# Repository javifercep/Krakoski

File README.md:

# Krakoski
Kodillo compatible board

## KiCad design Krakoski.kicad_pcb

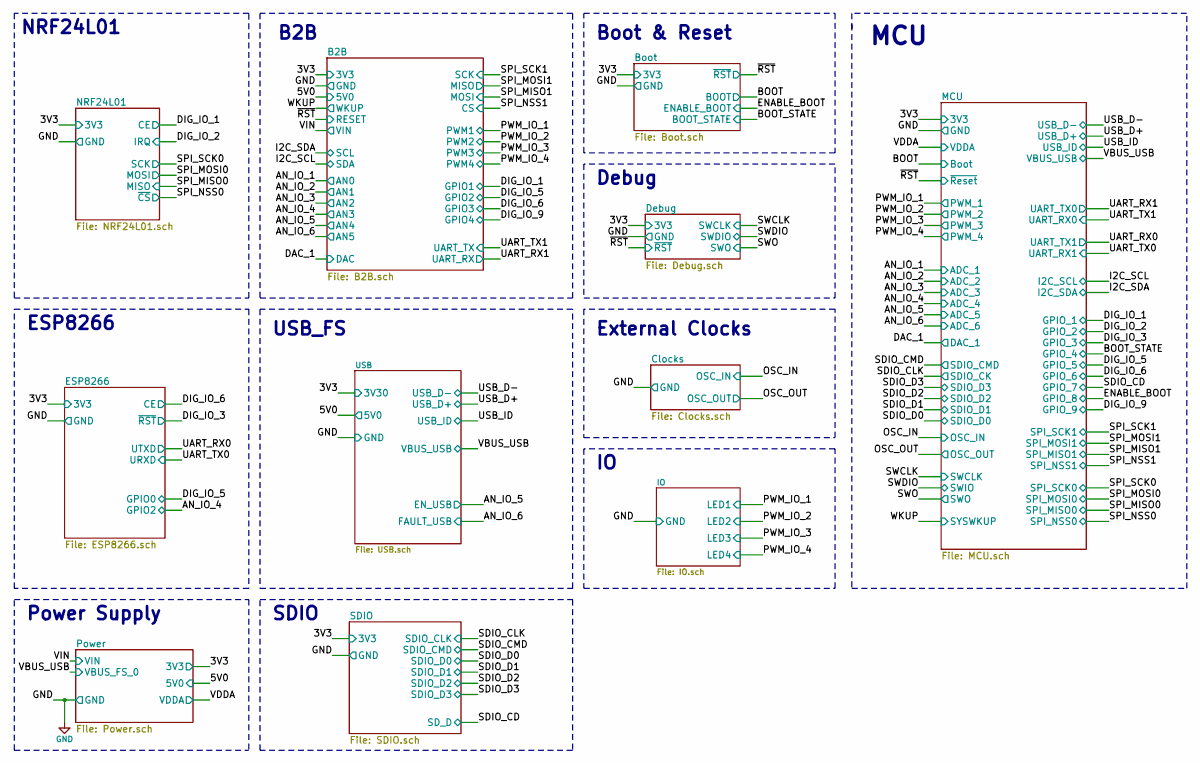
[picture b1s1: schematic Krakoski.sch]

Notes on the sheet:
Power Supply
USB_FS
Debug
External Clocks
MCU
Boot & Reset
ESP8266
B2B
NRF24L01
SDIO

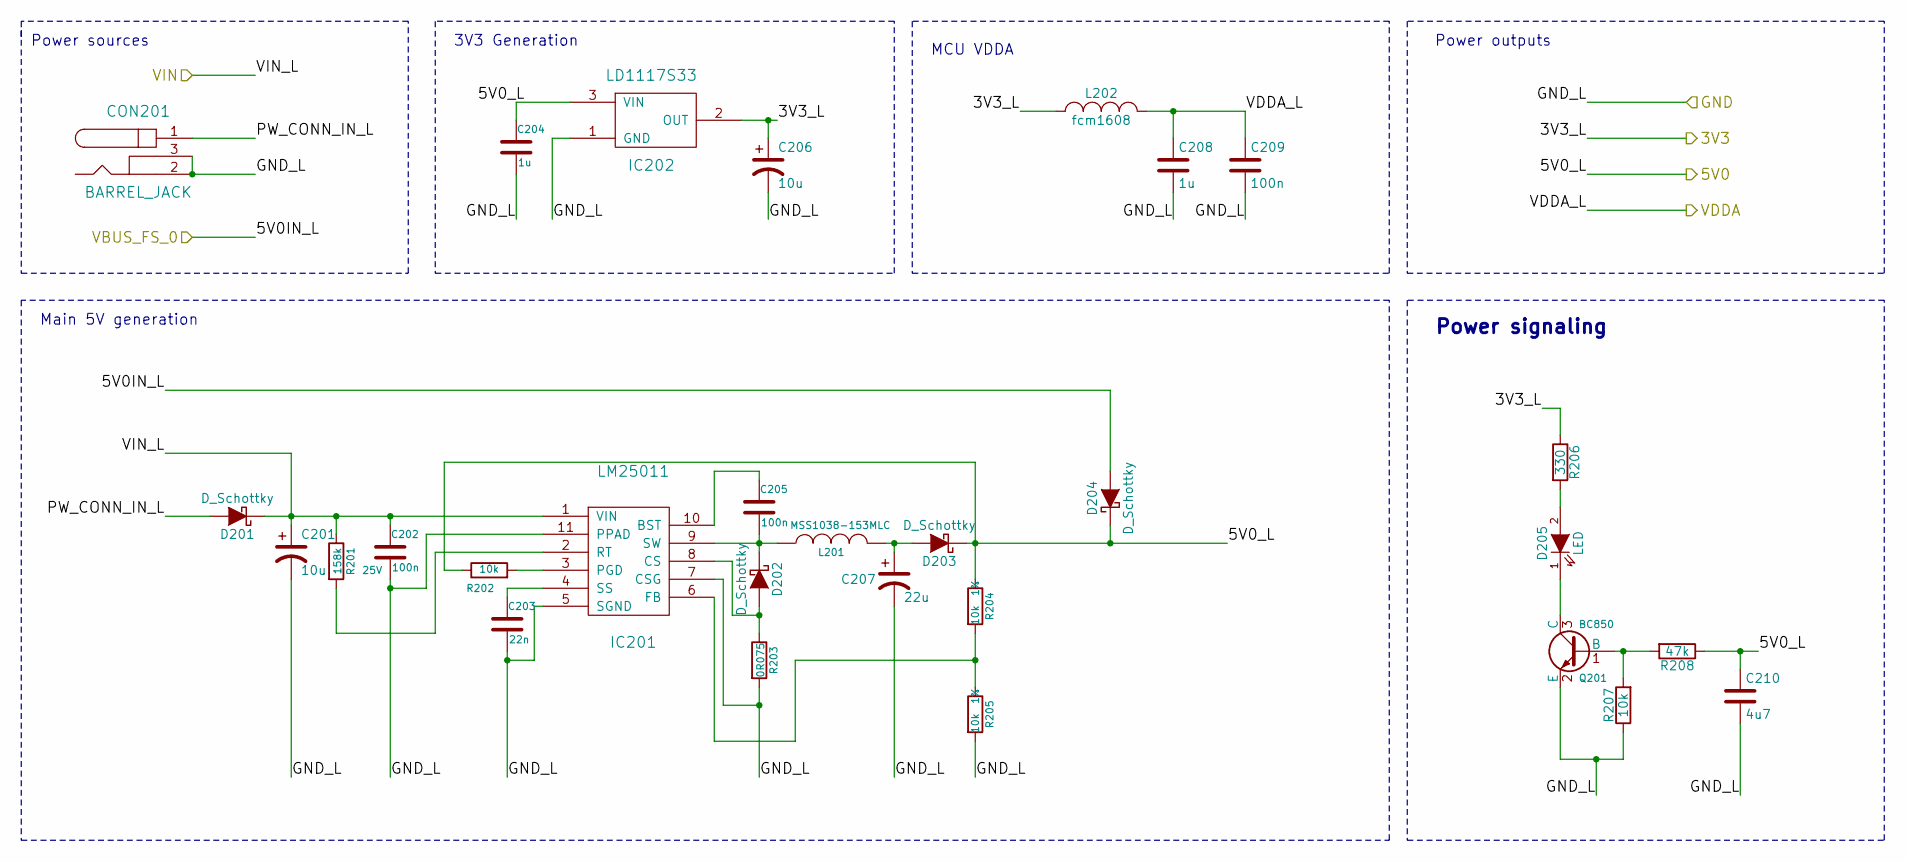
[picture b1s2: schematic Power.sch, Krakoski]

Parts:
C201: 10u; C_1206_HandSoldering
C202, C205: 100n; C_0805_HandSoldering
C203: 22n; C_0603_HandSoldering
C204, C208: 1u; C_0603_HandSoldering
C206: 10u; C_0603_HandSoldering
C207: 22u; C_1206_HandSoldering
C209: 100n; C_0603_HandSoldering
C210: 4u7; C_0805_HandSoldering
CON201: BARREL_JACK; JACK_ALIM_MOD
D201, D202, D203: D_Schottky; SMA_Handsoldering
D204: D_Schottky; SOD-123
D205: LED; LED-0805
IC201: LM25011; VSSOP10
IC202: LD1117S33; SOT-223
L201: MSS1038-153MLC; MSS1038
L202: fcm1608; R_0603_HandSoldering
Q201: BC850; SOT-23_Handsoldering
R201: 158k; R_0603_HandSoldering
R202, R207: 10k; R_0603_HandSoldering
R203: 0R075; R_0805_HandSoldering
R204, R205: 10k; R_0603_HandSoldering; Tolerancia 1%
R206: 330; R_0603_HandSoldering
R208: 47k; R_0603_HandSoldering

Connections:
/B2B/3V3: C206.1, IC202.2 (OUT), L202.1, R206.1; also elsewhere on the board
/B2B/5V0: C204.1, C210.1, D203.1 (K), D204.1 (K), IC202.3 (VIN), R202.1, R204.1, R208.1; also elsewhere on the board
/B2B/VIN: C201.1, C202.1, D201.1 (K), IC201.1 (VIN), R201.1; also elsewhere on the board
/MCU/VDDA: C208.1, C209.1, L202.2; also elsewhere on the board
/Power/PW_CONN_IN_L: CON201.1, D201.2 (A)
/Power/VBUS_FS_0: D204.2 (A); also elsewhere on the board
GND: C201.2, C202.2, C203.2, C204.2, C206.2, C207.2, C208.2, C209.2, C210.2, CON201.2, CON201.3, IC201.5 (SGND), IC201.7 (CSG), IC201.11 (PPAD), IC202.1 (GND), Q201.2 (E), R203.2, R205.2, R207.1; also elsewhere on the board
unnamed: C203.1, IC201.4 (SS)
unnamed: C205.1, IC201.10 (BST)
unnamed: C205.2, D202.1 (K), IC201.9 (SW), L201.1
unnamed: C207.1, D203.2 (A), L201.2
unnamed: D202.2 (A), IC201.8 (CS), R203.1
unnamed: D205.1 (K), Q201.3 (C)
unnamed: D205.2 (A), R206.2
unnamed: IC201.2 (RT), R201.2
unnamed: IC201.3 (PGD), R202.2
unnamed: IC201.6 (FB), R204.2, R205.1
unnamed: Q201.1 (B), R207.2, R208.2

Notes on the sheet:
Power sources
Main 5V generation
3V3 Generation
Power outputs
Power signaling
MCU VDDA

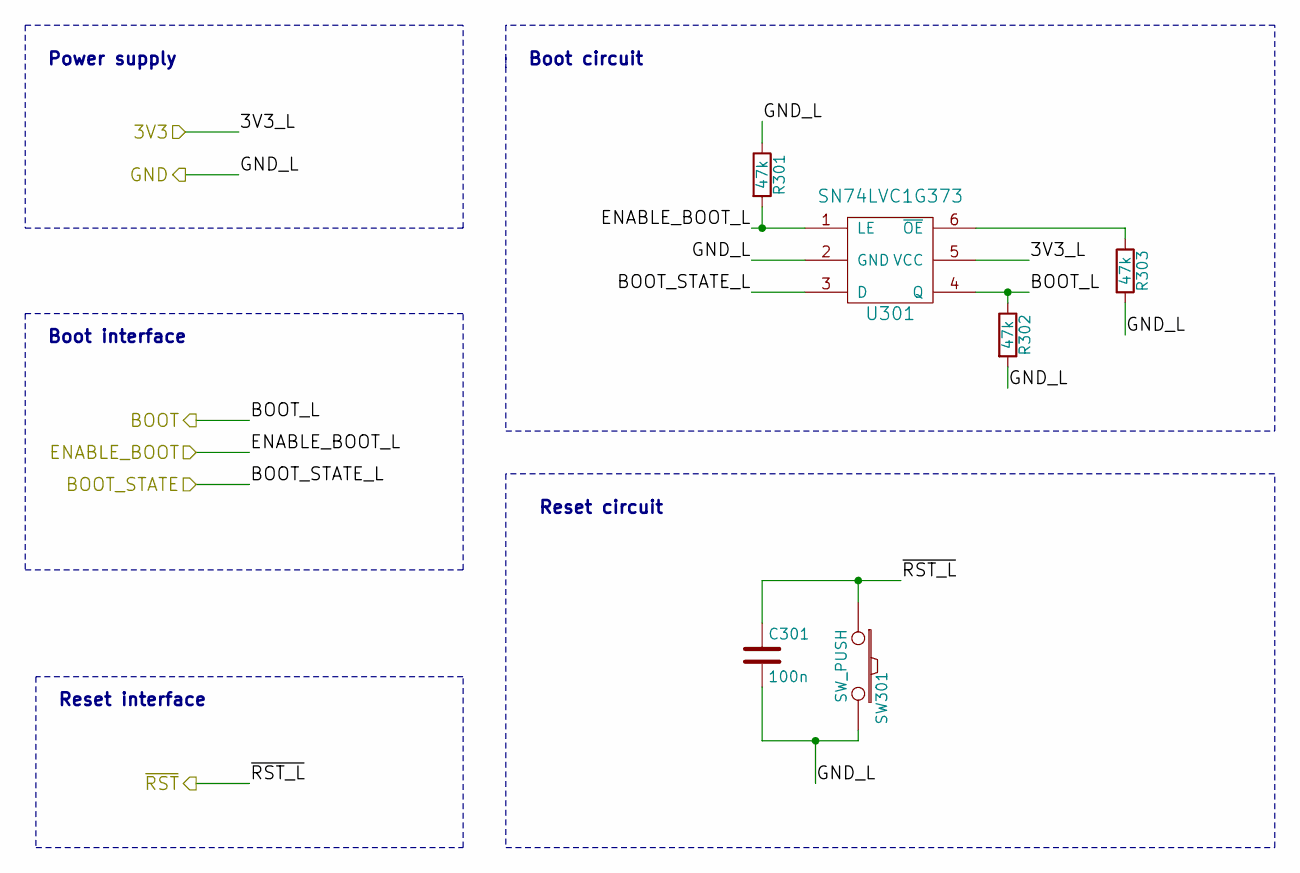
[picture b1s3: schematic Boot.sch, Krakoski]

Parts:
C301: 100n; C_0603_HandSoldering
R301, R302, R303: 47k; R_0603_HandSoldering
SW301: SW_PUSH; SW_PUSH_SMALL_SMD
U301: SN74LVC1G373; SOT-23-6

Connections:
/B2B/3V3: U301.5 (VCC); also elsewhere on the board
/B2B/RESET: C301.1, SW301.1; also elsewhere on the board
/Boot/BOOT: R302.1, U301.4 (Q); also elsewhere on the board
/Boot/BOOT_STATE: U301.3 (D); also elsewhere on the board
/Boot/ENABLE_BOOT: R301.2, U301.1 (LE); also elsewhere on the board
GND: C301.2, R301.1, R302.2, R303.2, SW301.2, U301.2 (GND); also elsewhere on the board
unnamed: R303.1, U301.6 (~OE)

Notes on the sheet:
Reset circuit
Boot circuit
Power supply
Boot interface
Reset interface

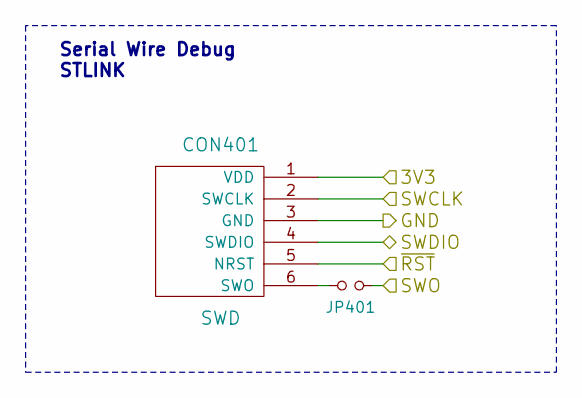
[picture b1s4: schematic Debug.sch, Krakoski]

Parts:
CON401: SWD; Pin_Header_Straight_1x06
JP401: Jumper_NO_Small; R_0603_HandSoldering

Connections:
/B2B/3V3: CON401.1 (VDD); also elsewhere on the board
/B2B/RESET: CON401.5 (NRST); also elsewhere on the board
/Debug/SWCLK: CON401.2 (SWCLK); also elsewhere on the board
/Debug/SWDIO: CON401.4 (SWDIO); also elsewhere on the board
/Debug/SWO: JP401.2; also elsewhere on the board
GND: CON401.3 (GND); also elsewhere on the board
unnamed: CON401.6 (SWO), JP401.1

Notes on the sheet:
Serial Wire Debug STLINK

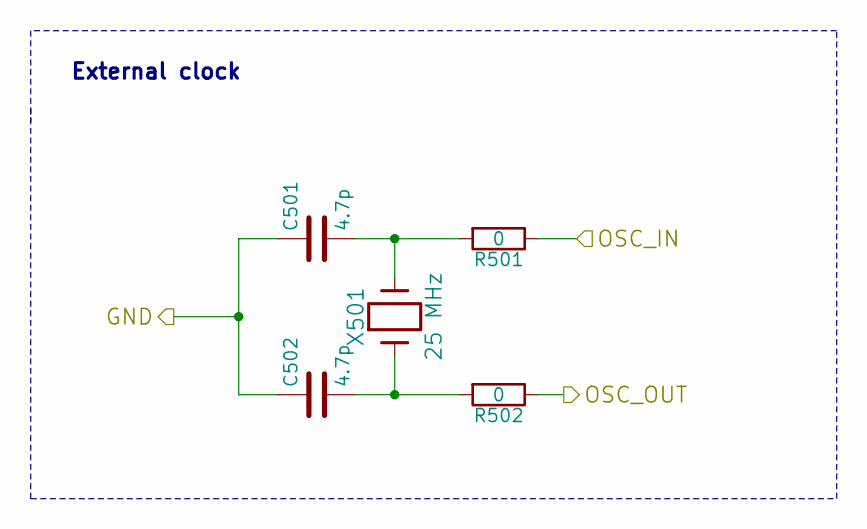
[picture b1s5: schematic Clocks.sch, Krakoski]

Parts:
C501, C502: 4.7p; C_0603_HandSoldering
R501, R502: 0; R_0603_HandSoldering
X501: 25 MHz; 7A-25.000MAAJ-T

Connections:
/Clocks/OSC_IN: R501.1; also elsewhere on the board
/Clocks/OSC_OUT: R502.1; also elsewhere on the board
GND: C501.1, C502.1; also elsewhere on the board
unnamed: C501.2, R501.2, X501.2
unnamed: C502.2, R502.2, X501.1

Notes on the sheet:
External clock

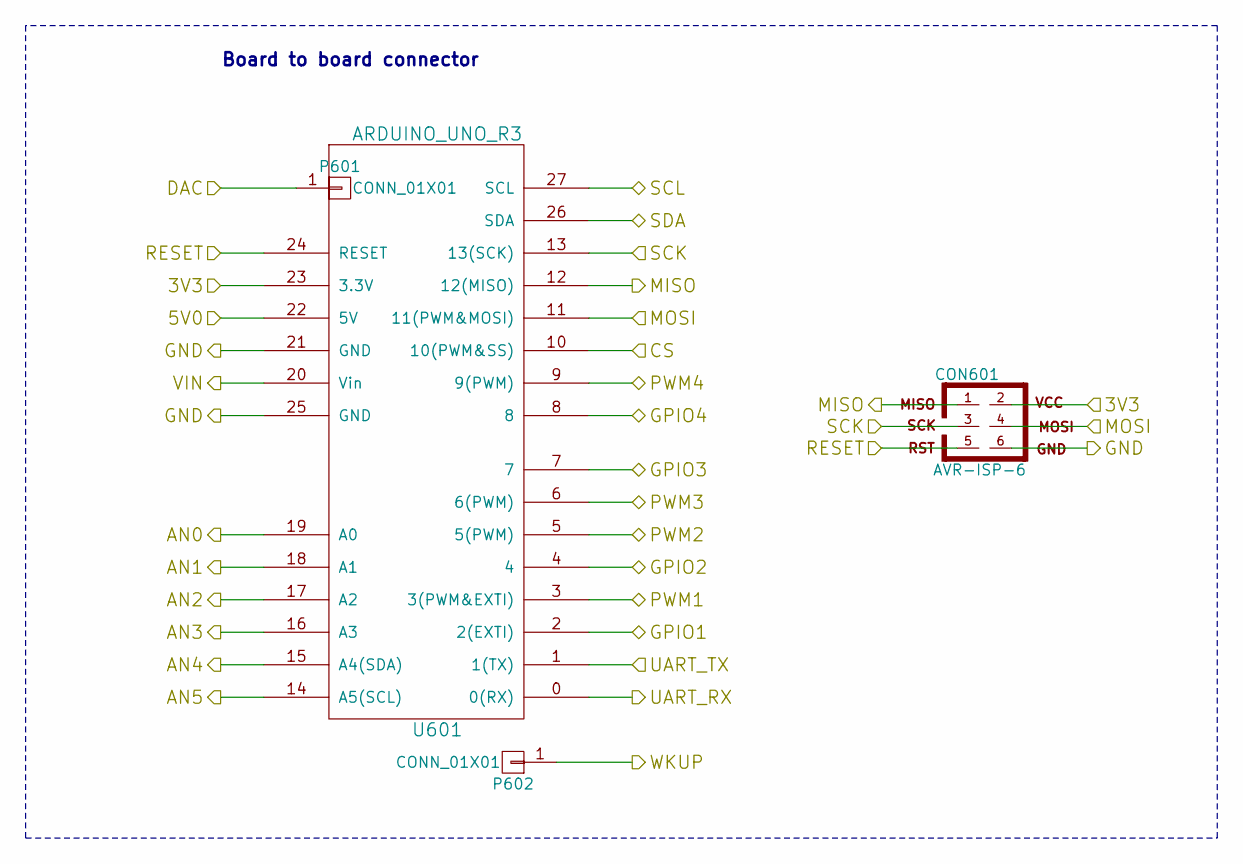
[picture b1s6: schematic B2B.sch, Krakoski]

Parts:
CON601: AVR-ISP-6; Pin_Header_Straight_2x03
P601, P602: CONN_01X01; Socket_Strip_Straight_1x01
U601: ARDUINO_UNO_R3; ArduinoUNOShieldR3

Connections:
/B2B/3V3: CON601.2, U601.23 (3.3V); also elsewhere on the board
/B2B/5V0: U601.22 (5V); also elsewhere on the board
/B2B/CS: U601.10 (10(PWM&SS)); also elsewhere on the board
/B2B/GPIO4: U601.8; also elsewhere on the board
/B2B/MISO: CON601.1, U601.12 (12(MISO)); also elsewhere on the board
/B2B/MOSI: CON601.4, U601.11 (11(PWM&MOSI)); also elsewhere on the board
/B2B/RESET: CON601.5, U601.24 (RESET); also elsewhere on the board
/B2B/SCK: CON601.3, U601.13 (13(SCK)); also elsewhere on the board
/B2B/UART_RX: U601.0 (0(RX)); also elsewhere on the board
/B2B/VIN: U601.20 (Vin); also elsewhere on the board
/ESP8266/CE: U601.7; also elsewhere on the board
/ESP8266/GPIO0: U601.4; also elsewhere on the board
/IO/LED1: U601.3 (3(PWM&EXTI)); also elsewhere on the board
/IO/LED2: U601.5 (5(PWM)); also elsewhere on the board
/IO/LED3: U601.6 (6(PWM)); also elsewhere on the board
/IO/LED4: U601.9 (9(PWM)); also elsewhere on the board
/MCU/ADC_1: U601.19 (A0); also elsewhere on the board
/MCU/ADC_2: U601.18 (A1); also elsewhere on the board
/MCU/ADC_3: U601.17 (A2); also elsewhere on the board
/MCU/ADC_4: U601.16 (A3); also elsewhere on the board
/MCU/ADC_5: U601.15 (A4(SDA)); also elsewhere on the board
/MCU/ADC_6: U601.14 (A5(SCL)); also elsewhere on the board
/MCU/I2C_SCL: U601.26 (SDA); also elsewhere on the board
/MCU/I2C_SDA: U601.27 (SCL); also elsewhere on the board
/MCU/UART_RX0: U601.1 (1(TX)); also elsewhere on the board
/NRF24L01/CE: U601.2 (2(EXTI)); also elsewhere on the board
GND: CON601.6, U601.21 (GND), U601.25 (GND); also elsewhere on the board

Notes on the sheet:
Board to board connector

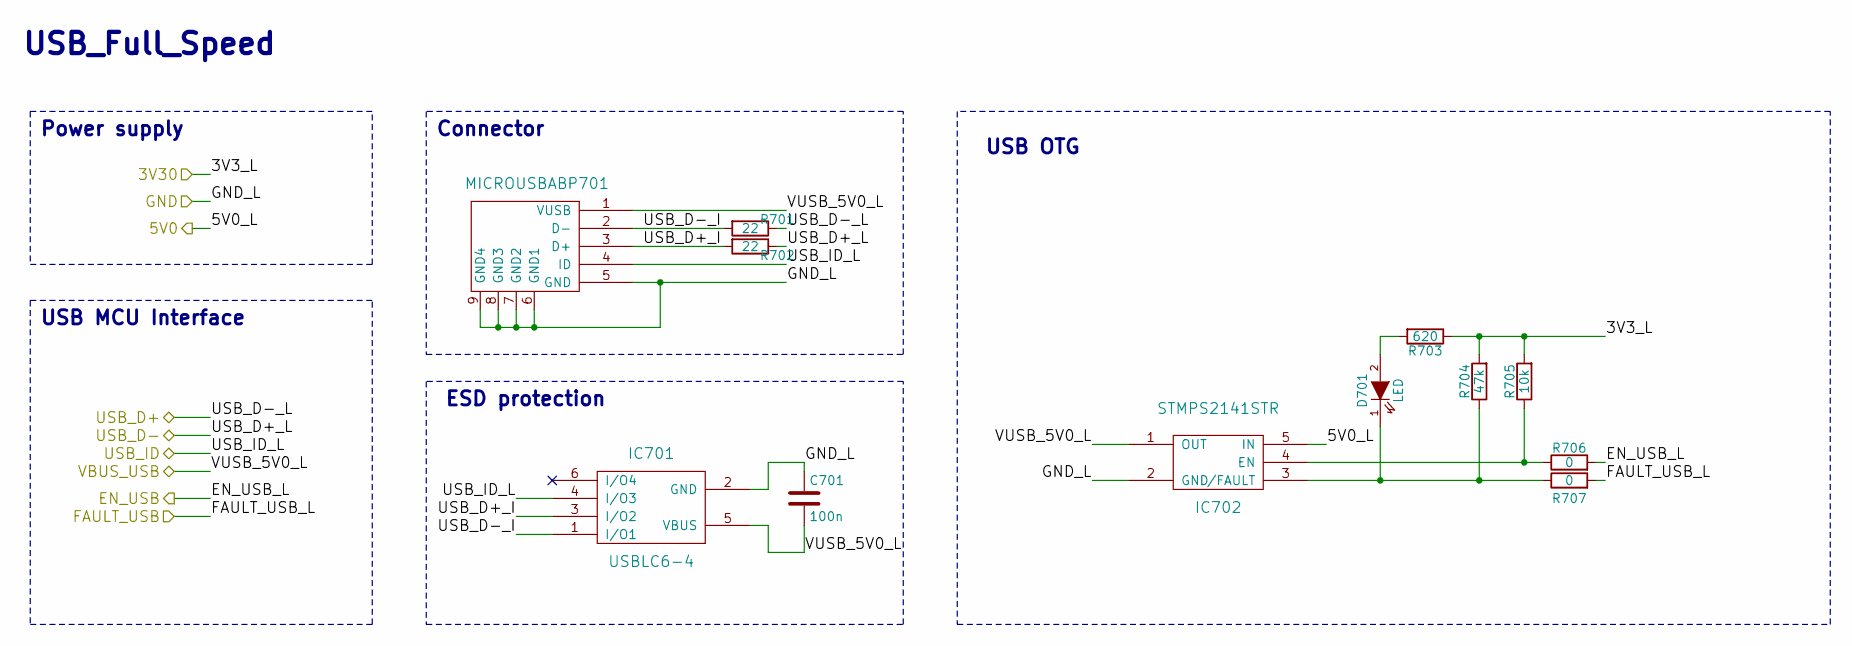
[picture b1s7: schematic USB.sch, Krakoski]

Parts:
C701: 100n; C_0603_HandSoldering
D701: LED; LED-0805
IC701: USBLC6-4; SOT-23-6
IC702: STMPS2141STR; SOT-23-5
P701: MICROUSBAB; uUSB-AB
R701, R702: 22; R_0603_HandSoldering
R703: 620; R_0603_HandSoldering
R704: 47k; R_0603_HandSoldering
R705: 10k; R_0603_HandSoldering
R706, R707: 0; R_0603_HandSoldering

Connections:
/B2B/3V3: R703.1, R704.2, R705.2; also elsewhere on the board
/B2B/5V0: IC702.5 (IN); also elsewhere on the board
/MCU/ADC_5: R706.2; also elsewhere on the board
/MCU/ADC_6: R707.2; also elsewhere on the board
/MCU/USB_D+: R701.1; also elsewhere on the board
/MCU/USB_D-: R702.1; also elsewhere on the board
/MCU/USB_ID: IC701.4 (I/O3), P701.4 (ID); also elsewhere on the board
/Power/VBUS_FS_0: C701.2, IC701.5 (VBUS), IC702.1 (OUT), P701.1 (VUSB); also elsewhere on the board
/USB/USB_D+_I: IC701.3 (I/O2), P701.3 (D+), R702.2
/USB/USB_D-_I: IC701.1 (I/O1), P701.2 (D-), R701.2
GND: C701.1, IC701.2 (GND), IC702.2 (GND), P701.5 (GND), P701.6 (GND1), P701.7 (GND2), P701.8 (GND3), P701.9 (GND4); also elsewhere on the board
unnamed: D701.1 (K), IC702.3 (/FAULT), R704.1, R707.1
unnamed: D701.2 (A), R703.2
unnamed: IC702.4 (EN), R705.1, R706.1

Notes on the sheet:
Power supply
USB_Full_Speed
Connector
ESD protection
USB MCU Interface
USB OTG

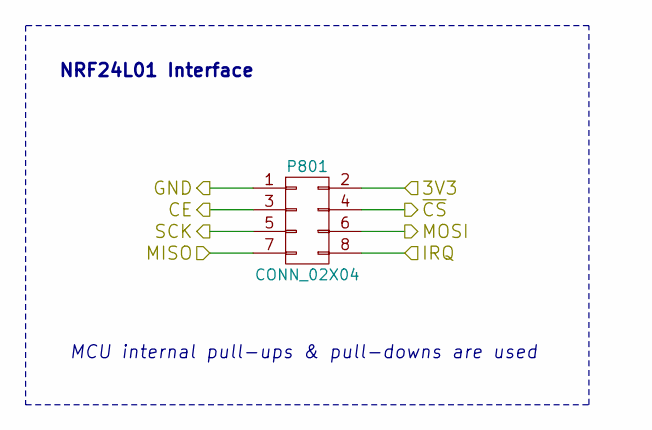
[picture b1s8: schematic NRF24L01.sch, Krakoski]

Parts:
P801: CONN_02X04; Socket_Strip_Straight_2x04

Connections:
/B2B/3V3: P801.2; also elsewhere on the board
/MCU/GPIO_2: P801.8; also elsewhere on the board
/MCU/SPI_NSS0: P801.4; also elsewhere on the board
/NRF24L01/CE: P801.3; also elsewhere on the board
/NRF24L01/MISO: P801.7; also elsewhere on the board
/NRF24L01/MOSI: P801.6; also elsewhere on the board
/NRF24L01/SCK: P801.5; also elsewhere on the board
GND: P801.1; also elsewhere on the board

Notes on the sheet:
MCU internal pull-ups & pull-downs are used
NRF24L01 Interface

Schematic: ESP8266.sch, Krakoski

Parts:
P901: CONN_02X04; Socket_Strip_Straight_2x04

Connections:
/B2B/3V3: P901.7; also elsewhere on the board
/ESP8266/CE: P901.3; also elsewhere on the board
/ESP8266/GPIO0: P901.6; also elsewhere on the board
/MCU/ADC_4: P901.4; also elsewhere on the board
/MCU/GPIO_3: P901.5; also elsewhere on the board
/MCU/UART_RX1: P901.8; also elsewhere on the board
/MCU/UART_TX1: P901.1; also elsewhere on the board
GND: P901.2; also elsewhere on the board

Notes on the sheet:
MCU internal pull-ups & pull-downs are used
ESP8266 Interface

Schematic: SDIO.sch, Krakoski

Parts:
R1001, R1002, R1003, R1004, R1005: 47K; R_0603_HandSoldering
R1006: 0; R_0603_HandSoldering
U1001: SD_CARD; uSDCard

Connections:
/B2B/3V3: R1001.2, R1002.2, R1003.2, R1004.2, R1005.2, U1001.4 (VDD); also elsewhere on the board
/MCU/GPIO_7: R1006.2; also elsewhere on the board
/MCU/SDIO_CK: U1001.5 (CLK); also elsewhere on the board
/MCU/SDIO_CMD: R1001.1, U1001.3 (CMD); also elsewhere on the board
/MCU/SDIO_D0: R1002.1, U1001.7 (DAT0); also elsewhere on the board
/MCU/SDIO_D1: R1003.1, U1001.8 (DAT1); also elsewhere on the board
/MCU/SDIO_D2: R1004.1, U1001.1 (DAT2); also elsewhere on the board
/MCU/SDIO_D3: R1005.1, U1001.2 (CD/DAT3); also elsewhere on the board
/SDIO/CD: R1006.1, U1001.10 (CD)
GND: U1001.6 (VSS), U1001.9 (DL(GND)); also elsewhere on the board

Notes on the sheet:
SD Card Connector
Power supply
SDIO interface
SD Card detection

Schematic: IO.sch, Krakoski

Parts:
D1101, D1102, D1103, D1104: LED; LED-0805
R1101, R1102, R1103, R1104: 510; R_0603_HandSoldering

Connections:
/IO/LED1: R1101.2; also elsewhere on the board
/IO/LED2: R1102.2; also elsewhere on the board
/IO/LED3: R1103.2; also elsewhere on the board
/IO/LED4: R1104.2; also elsewhere on the board
GND: D1101.1 (K), D1102.1 (K), D1103.1 (K), D1104.1 (K); also elsewhere on the board
unnamed: D1101.2 (A), R1101.1
unnamed: D1102.2 (A), R1102.1
unnamed: D1103.2 (A), R1103.1
unnamed: D1104.2 (A), R1104.1

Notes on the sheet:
On board LEDs

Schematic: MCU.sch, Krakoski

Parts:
C1201, C1202: 2u2; C_0805_HandSoldering
C1203, C1204, C1205, C1206, C1208: 100n; C_0603_HandSoldering
C1207: 1u; C_0603_HandSoldering
C1209: 4,7u; C_0603_HandSoldering
R1201: 0; R_0603_HandSoldering
R1202: 1K; R_0603_HandSoldering
R1203: 47; R_0603_HandSoldering
U1201: STM32F205RCTX; LQFP-64_10x10mm_Pitch0.5mm

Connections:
/B2B/3V3: C1203.1, C1204.1, C1205.1, C1206.1, C1208.1, C1209.1, R1203.2, U1201.19 (VDD), U1201.32 (VDD), U1201.48 (VDD), U1201.64 (VDD); also elsewhere on the board
/B2B/CS: U1201.28 (PB2); also elsewhere on the board
/B2B/DAC: U1201.20 (PA4); also elsewhere on the board
/B2B/GPIO4: U1201.50 (PA15); also elsewhere on the board
/B2B/MISO: U1201.23 (PA7); also elsewhere on the board
/B2B/MOSI: U1201.22 (PA6); also elsewhere on the board
/B2B/RESET: U1201.7 (NRST); also elsewhere on the board
/B2B/SCK: U1201.21 (PA5); also elsewhere on the board
/B2B/UART_RX: U1201.16 (PA2); also elsewhere on the board
/Boot/BOOT: R1201.2; also elsewhere on the board
/Boot/BOOT_STATE: U1201.3 (PC14); also elsewhere on the board
/Boot/ENABLE_BOOT: U1201.8 (PC0); also elsewhere on the board
/Clocks/OSC_IN: U1201.5 (PH0); also elsewhere on the board
/Clocks/OSC_OUT: U1201.6 (PH1); also elsewhere on the board
/Debug/SWCLK: U1201.49 (PA14); also elsewhere on the board
/Debug/SWDIO: U1201.46 (PA13); also elsewhere on the board
/Debug/SWO: U1201.55 (PB3); also elsewhere on the board
/ESP8266/CE: U1201.15 (PA1); also elsewhere on the board
/ESP8266/GPIO0: U1201.2 (PC13); also elsewhere on the board
/IO/LED1: U1201.56 (PB4); also elsewhere on the board
/IO/LED2: U1201.57 (PB5); also elsewhere on the board
/IO/LED3: U1201.30 (PB11); also elsewhere on the board
/IO/LED4: U1201.29 (PB10); also elsewhere on the board
/MCU/ADC_1: U1201.10 (PC2); also elsewhere on the board
/MCU/ADC_2: U1201.11 (PC3); also elsewhere on the board
/MCU/ADC_3: U1201.24 (PC4); also elsewhere on the board
/MCU/ADC_4: U1201.25 (PC5); also elsewhere on the board
/MCU/ADC_5: U1201.26 (PB0); also elsewhere on the board
/MCU/ADC_6: U1201.27 (PB1); also elsewhere on the board
/MCU/BOOT_L: R1201.1, R1202.2, U1201.60 (BOOT0)
/MCU/GPIO_2: U1201.37 (PC6); also elsewhere on the board
/MCU/GPIO_3: U1201.4 (PC15); also elsewhere on the board
/MCU/GPIO_7: U1201.9 (PC1); also elsewhere on the board
/MCU/I2C_SCL: U1201.61 (PB8); also elsewhere on the board
/MCU/I2C_SDA: U1201.62 (PB9); also elsewhere on the board
/MCU/SDIO_CK: U1201.53 (PC12); also elsewhere on the board
/MCU/SDIO_CMD: U1201.54 (PD2); also elsewhere on the board
/MCU/SDIO_D0: U1201.39 (PC8); also elsewhere on the board
/MCU/SDIO_D1: U1201.40 (PC9); also elsewhere on the board
/MCU/SDIO_D2: U1201.51 (PC10); also elsewhere on the board
/MCU/SDIO_D3: U1201.52 (PC11); also elsewhere on the board
/MCU/SPI_NSS0: U1201.33 (PB12); also elsewhere on the board
/MCU/SYSWKUP: U1201.14 (PA0_WKUP); also elsewhere on the board
/MCU/UART_RX0: U1201.17 (PA3); also elsewhere on the board
/MCU/UART_RX1: U1201.59 (PB7); also elsewhere on the board
/MCU/UART_TX1: U1201.58 (PB6); also elsewhere on the board
/MCU/USB_D+: U1201.45 (PA12); also elsewhere on the board
/MCU/USB_D-: U1201.44 (PA11); also elsewhere on the board
/MCU/USB_ID: U1201.43 (PA10); also elsewhere on the board
/MCU/VBAT_L: C1207.1, R1203.1, U1201.1 (VBAT)
/MCU/VCAP_1: C1201.1, U1201.31 (VCAP_1)
/MCU/VCAP_2: C1202.1, U1201.47 (VCAP_2)
/MCU/VDDA: U1201.13 (VDDA); also elsewhere on the board
/NRF24L01/CE: U1201.38 (PC7); also elsewhere on the board
/NRF24L01/MISO: U1201.35 (PB14); also elsewhere on the board
/NRF24L01/MOSI: U1201.36 (PB15); also elsewhere on the board
/NRF24L01/SCK: U1201.34 (PB13); also elsewhere on the board
/Power/VBUS_FS_0: U1201.42 (PA9); also elsewhere on the board
GND: C1201.2, C1202.2, C1203.2, C1204.2, C1205.2, C1206.2, C1207.2, C1208.2, C1209.2, R1202.1, U1201.12 (VSSA), U1201.18 (VSS), U1201.63 (VSS); also elsewhere on the board

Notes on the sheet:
MCU: STM32F405 / STM32F205 / STM32F105
Power inputs
Decoupling capacitors
Reset & boot
External Clock
USB_FS
Debug & SYS
UART & USART
SPI
I2C
MCU MAPPING
Power scheme adaptor STM32F105/STM32F405
VBAT stabilization
PA10, PA9 & PA8 reserved for future improvements - USB OTG
PWM
SDIO

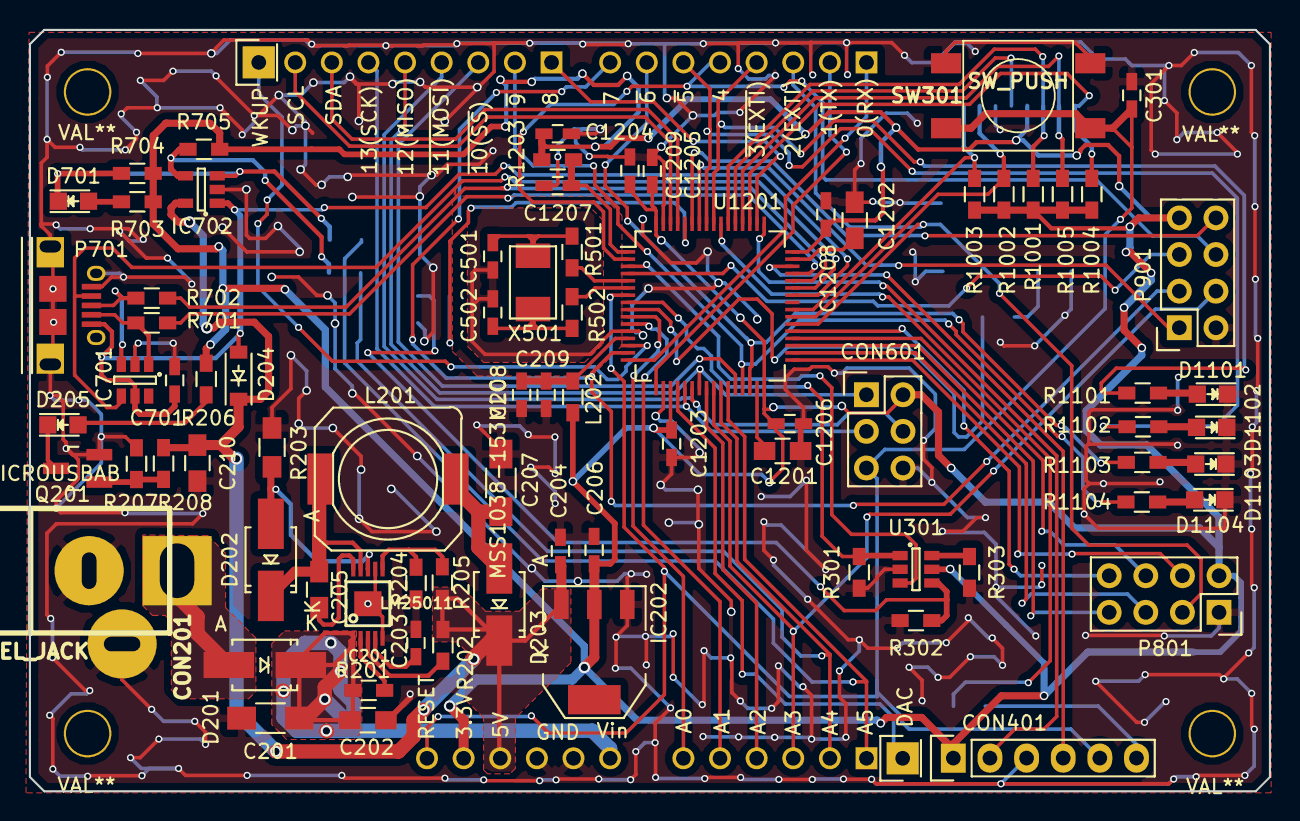
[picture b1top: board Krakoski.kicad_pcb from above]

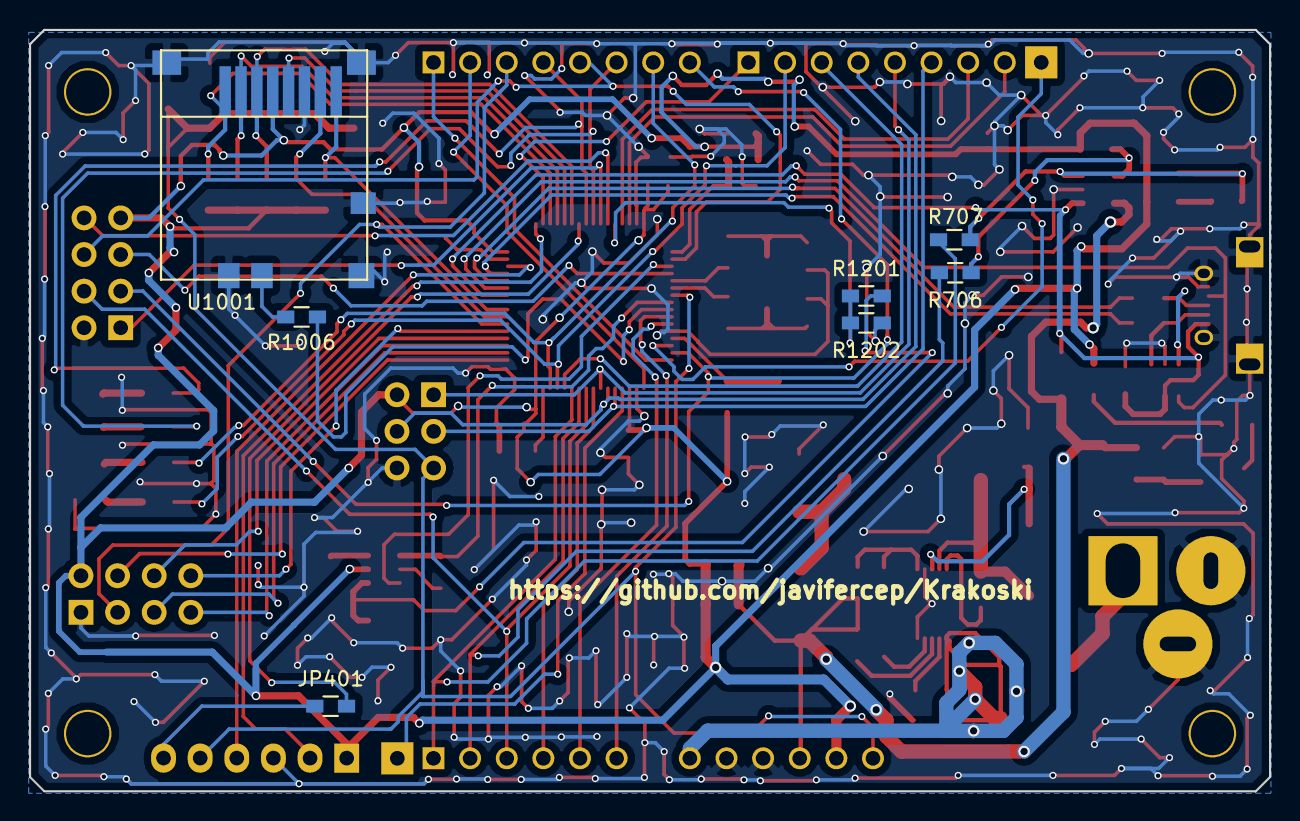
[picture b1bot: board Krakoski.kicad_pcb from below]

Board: 2 copper layers, 86.0 x 52.8 mm, 92 parts (7 on the bottom side), 87 nets.

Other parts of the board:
3MMDRILL, 3MMDRILL#2, 3MMDRILL#3, 3MMDRILL#4: VAL**; 3MMDRILL
DAC: CONN_01X01; Socket_Strip_Straight_1x01
WKUP: CONN_01X01; Socket_Strip_Straight_1x01

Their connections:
/B2B/DAC: DAC.1; also elsewhere on the board
/MCU/SYSWKUP: WKUP.1; also elsewhere on the board

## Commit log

2015-11-07 Added license and gitignore
2015-12-01 First krakoski output.
2015-12-08 Release 1.0.0
